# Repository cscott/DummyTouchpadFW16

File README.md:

# Dummy Touchpad Input Module

This is a dummy touchpad.  All it does is contain the resistors and pads to
tell the FW16 that there is a touchpad installed (though there is not).
It also brings the signal lines out to a 2.54mm SMT header, but that's
mostly for debugging/development, not for any real use.

If you are using this in conjunction with a
[full width touchpad spacer](https://github.com/cscott/TouchpadSpacerFW16)
don't populate the header.

Here's the [schematic](./MinimalSmallInputModule.pdf).

## License
Input Modules © 2023 by Framework Computer Inc is licensed under CC BY 4.0. To view a copy of this license, visit http://creativecommons.org/licenses/by/4.0/

## Fabrication and Assembly
Use a 0.8mm PCB for Input Modules.

As with the Framework [example](https://github.com/FrameworkComputer/InputModules/tree/main/Electrical/MicrocontrollerInputModule) use Keystone 24929
"zero height threaded inserts" ([available from Digikey](https://www.digikey.com/en/products/detail/keystone-electronics/24929/16343672))
where indicated, with the "big" side down.  These are soldered in place
and provide enough steel to engage properly with the magnets on the
FW16 midplate to hold the PCB in place.

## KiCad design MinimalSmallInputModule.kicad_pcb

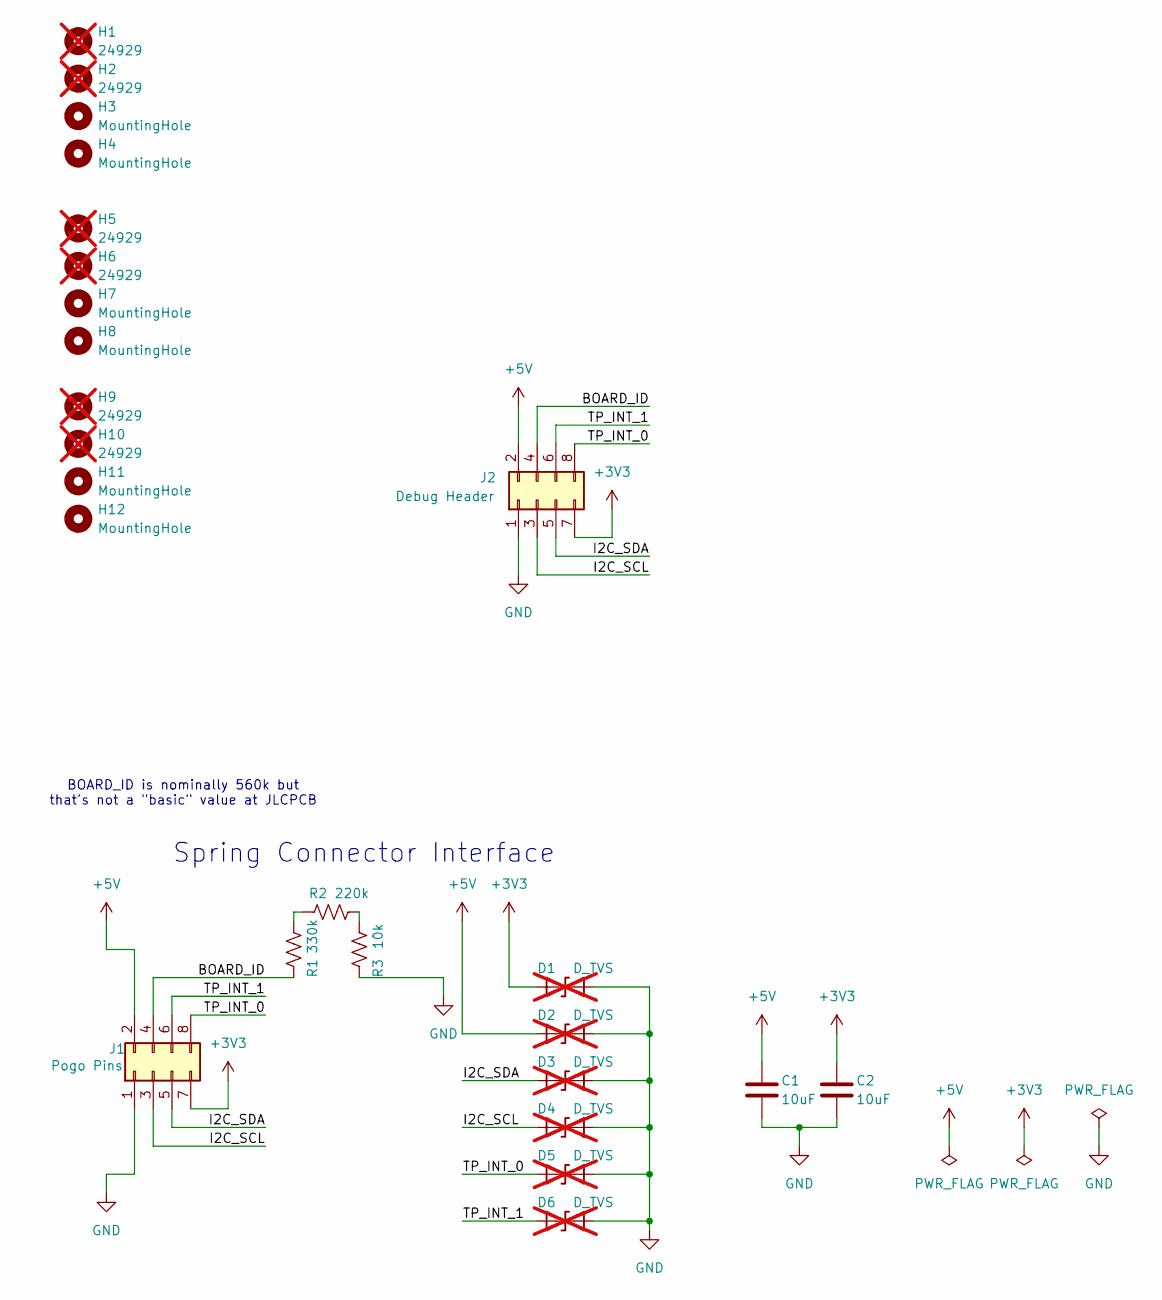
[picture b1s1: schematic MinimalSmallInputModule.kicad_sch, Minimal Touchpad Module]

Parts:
C1, C2: 10uF; C_0603_1608Metric; Digikey 1276-1869-1-ND
D1, D2, D3, D4, D5, D6: D_TVS; D_0402_1005Metric; Digikey F9744CT-ND; not fitted
H1, H2, H5, H6, H9, H10: 24929; MountingHole_3.7mm_Pad_24929; Digikey 36-24929CT-ND; not fitted
H3, H4, H7, H8, H11, H12: MountingHole; MountingHole_2.1mm
J1: Pogo Pins; PogoPads_2x4_P2.0mm
J2: Debug Header; PinHeader_2x04_P2.54mm_Vertical_SMD; LCSC C3294462
R1: 330k; R_0603_1608Metric; LCSC C23137
R2: 220k; R_0603_1608Metric; LCSC C22961
R3: 10k; R_0603_1608Metric; LCSC C25804

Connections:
+3V3: C2.1, D1.2 (A2), J1.7, J2.7
+5V: C1.1, D2.2 (A2), J1.2, J2.2
/BOARD_ID: J1.4, J2.4, R1.1
/I2C_SCL: D4.2 (A2), J1.3, J2.3
/I2C_SDA: D3.2 (A2), J1.5, J2.5
/TP_INT_0: D5.2 (A2), J1.8, J2.8
/TP_INT_1: D6.2 (A2), J1.6, J2.6
GND: C1.2, C2.2, D1.1 (A1), D2.1 (A1), D3.1 (A1), D4.1 (A1), D5.1 (A1), D6.1 (A1), J1.1, J2.1, R3.1
unnamed: R1.2, R2.2
unnamed: R2.1, R3.2

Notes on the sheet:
BOARD_ID is nominally 560k but that's not a "basic" value at JLCPCB
Spring Connector Interface

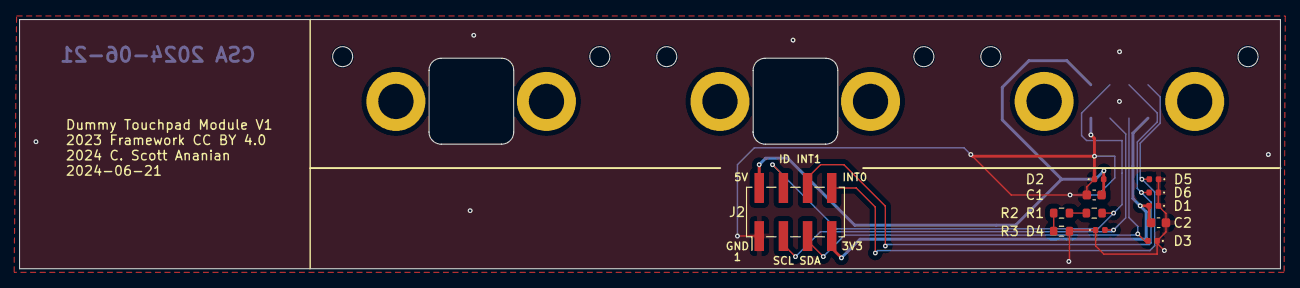
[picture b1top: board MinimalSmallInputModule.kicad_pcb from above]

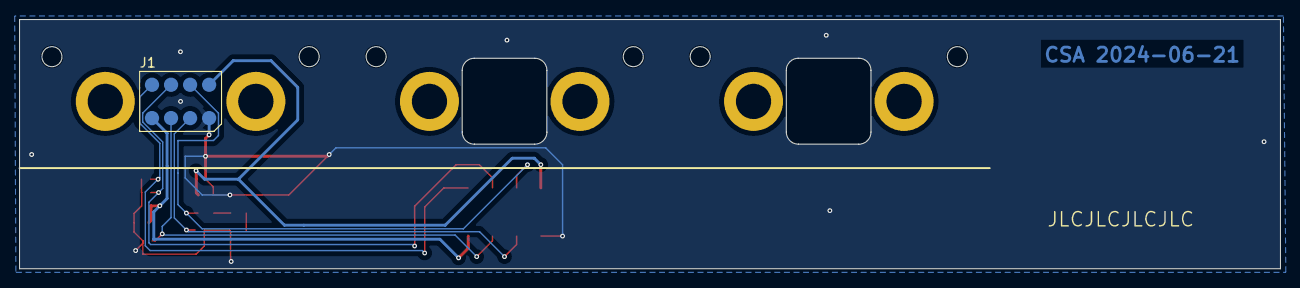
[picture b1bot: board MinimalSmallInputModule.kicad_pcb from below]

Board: 2 copper layers, 132.4 x 26.2 mm, 25 parts (7 on the bottom side), 10 nets.

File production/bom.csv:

Designator,Footprint,Quantity,Value,LCSC Part #
"C1, C2",0603,2,10uF,C96446
"H11, H12, H3, H4, H7, H8",MountingHole_2.1mm,6,MountingHole,
J1,PogoPads_2x4_P2.0mm,1,Pogo Pins,
J2,PinHeader_2x04_P2.54mm_Vertical_SMD,1,Debug Header,C3294462
R1,0603,1,330k,C23137
R2,0603,1,220k,C22961
R3,0603,1,10k,C25804

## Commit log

2024-06-21 Initial dummy touchpad module, forked from Framework Minimal Input Module
2024-06-21 First complete version sent to JLCPCB
2024-06-23 Add JLCJLCJLCJLC text (not yet used)
2024-07-07 Improve README, add PDF version of schematic
2024-07-25 Improve README, add image

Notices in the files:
MinimalSmallInputModule.kicad_pcb:
This work is licensed under a Creative Commons Attribution 4.0 International License
2023 Framework CC BY 4.0
